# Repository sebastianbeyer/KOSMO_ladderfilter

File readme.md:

A Kosmo version of the [Kassutronics transistor ladder filter](https://kassu2000.blogspot.com/2018/07/transistor-ladder-filter.html).

Find the documentation **and BOM** here: (https://github.com/kassu/kassutronics/tree/master/documentation/Transistor%20Ladder%20Filter)

You need to match the transistors, which is a bit boring. Those that I got where
already pretty close (within the recommended 2mV limit), but some outliers, so
maaaybe you could just try without matching.

# How to make the PCBs

Go download the latest gerber files [here](https://github.com/sebastianbeyer/KOSMO_ladderfilter/releases/latest).
Then send them to your favorite PCB Manufacturer (I use jlcpcb). Make sure you
check "Specify a location" at "Remove Order Number" for the panel.

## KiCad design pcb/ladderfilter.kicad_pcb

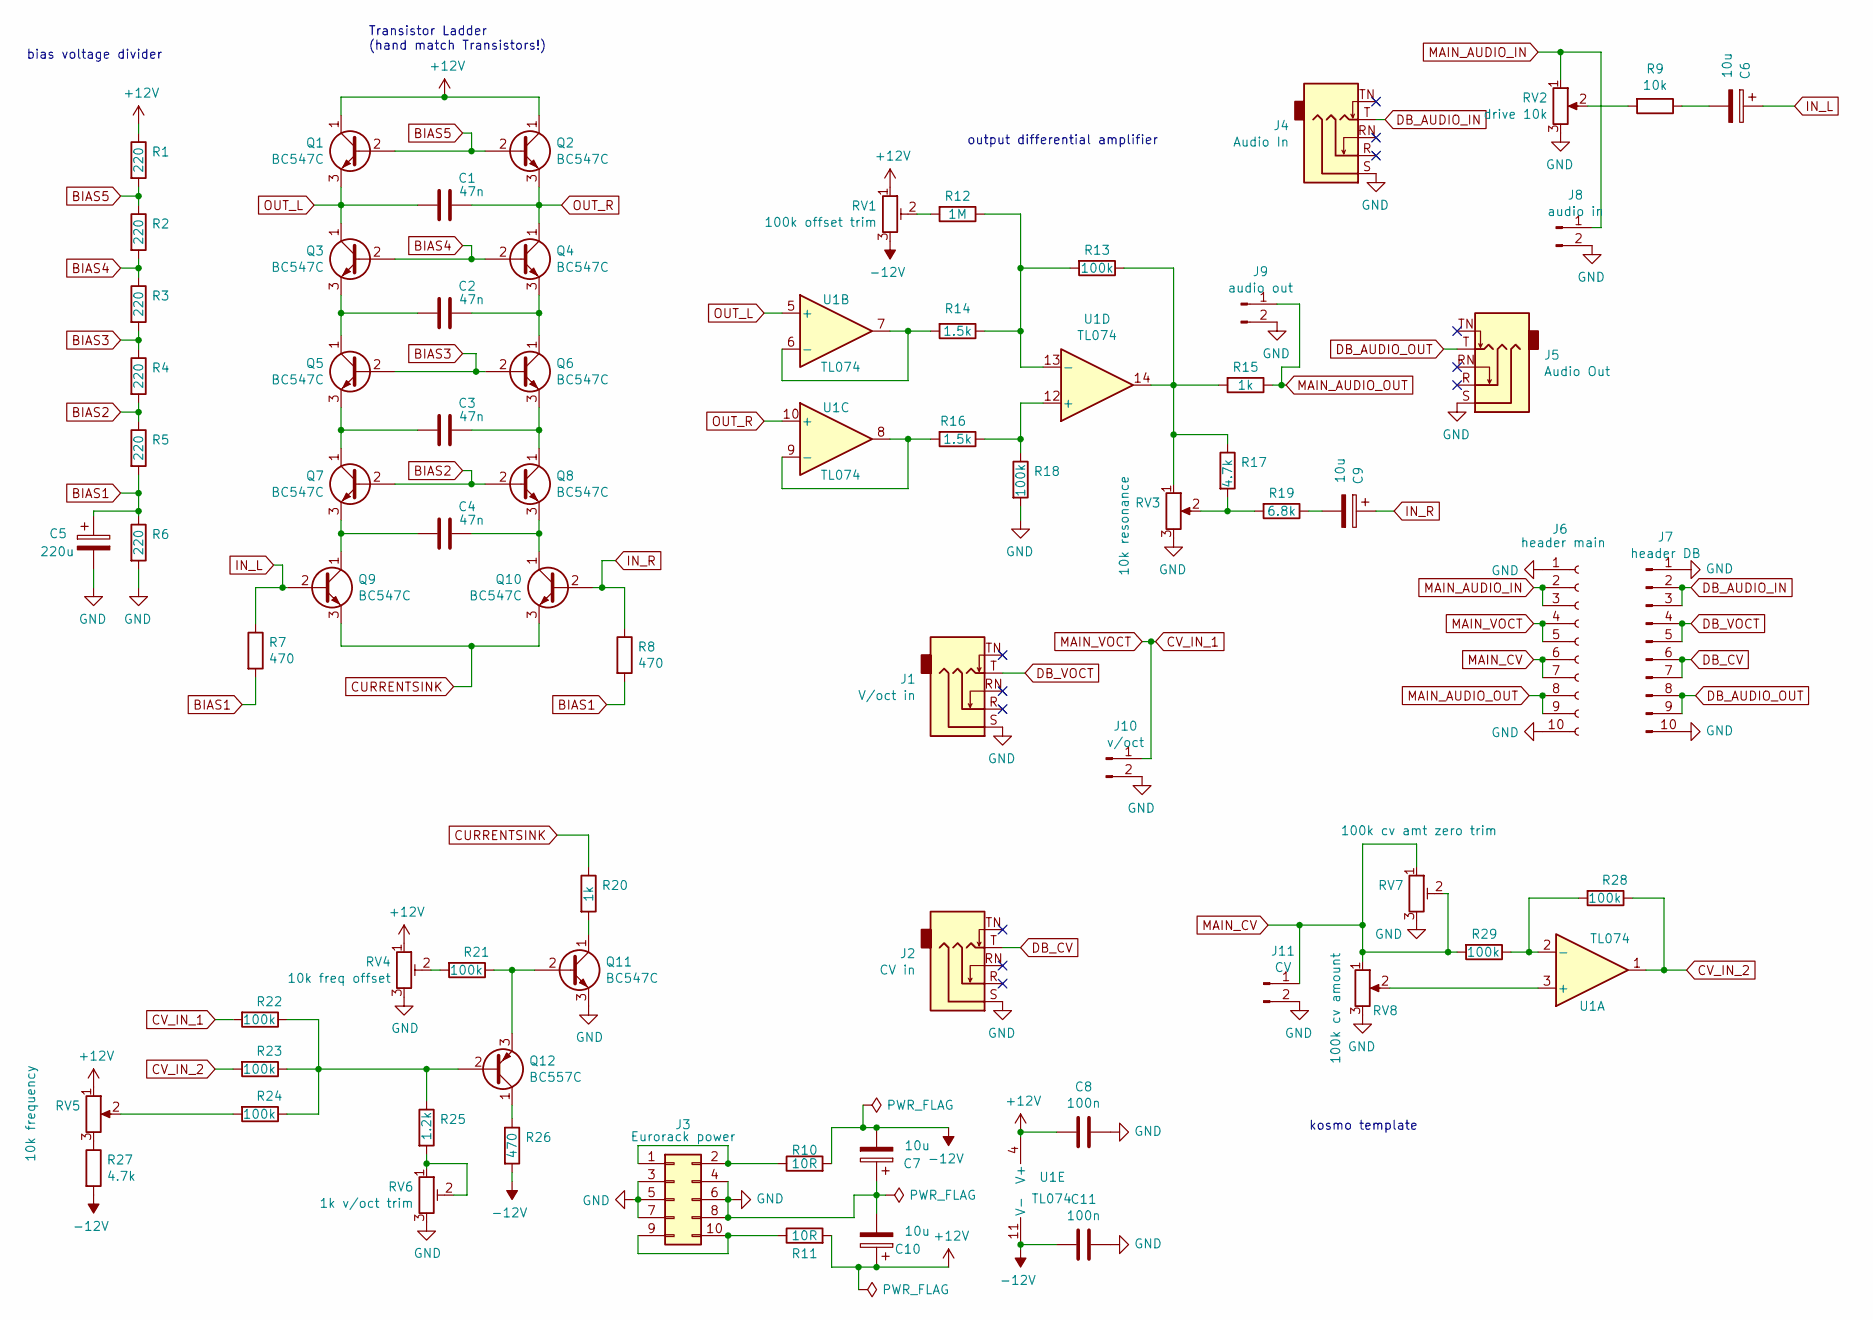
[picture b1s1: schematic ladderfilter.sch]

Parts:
C1, C2, C3, C4: 47n; C_Rect_L7.2mm_W2.5mm_P5.00mm_FKS2_FKP2_MKS2_MKP2
C5: 220u; CP_Radial_D5.0mm_P2.00mm
C6, C7, C9, C10: 10u; CP_Radial_D5.0mm_P2.00mm
C8, C11: 100n; C_Disc_D4.7mm_W2.5mm_P5.00mm
J1: V/oct in; Jack_6.35mm_PJ_629HAN
J2: CV in; Jack_6.35mm_PJ_629HAN
J3: Eurorack power; Multicomp_MC9A12-1034_2x05_P2.54mm_Vertical
J4: Audio In; Jack_6.35mm_PJ_629HAN
J5: Audio Out; Jack_6.35mm_PJ_629HAN
J6: header main; PinSocket_1x10_P2.54mm_Vertical
J7: header DB; PinHeader_1x10_P2.54mm_Vertical
J8: audio in; Molex_KK-254_AE-6410-02A_1x02_P2.54mm_Vertical
J9: audio out; Molex_KK-254_AE-6410-02A_1x02_P2.54mm_Vertical
J10: v/oct; Molex_KK-254_AE-6410-02A_1x02_P2.54mm_Vertical
J11: CV; Molex_KK-254_AE-6410-02A_1x02_P2.54mm_Vertical
Q1, Q2, Q3, Q4, Q5, Q6, Q7, Q8, Q9, Q10, Q11: BC547C; TO-92_Inline_Wide
Q12: BC557C; TO-92_Inline_Wide
R1, R2, R3, R4, R5, R6: 220; R_Axial_DIN0207_L6.3mm_D2.5mm_P7.62mm_Horizontal_silkvalue
R7, R8, R26: 470; R_Axial_DIN0207_L6.3mm_D2.5mm_P7.62mm_Horizontal_silkvalue
R9: 10k; R_Axial_DIN0207_L6.3mm_D2.5mm_P7.62mm_Horizontal_silkvalue
R10, R11: 10R; R_Axial_DIN0207_L6.3mm_D2.5mm_P7.62mm_Horizontal_silkvalue
R12: 1M; R_Axial_DIN0207_L6.3mm_D2.5mm_P7.62mm_Horizontal_silkvalue
R13, R18, R21, R22, R23, R24, R28, R29: 100k; R_Axial_DIN0207_L6.3mm_D2.5mm_P7.62mm_Horizontal_silkvalue
R14, R16: 1.5k; R_Axial_DIN0207_L6.3mm_D2.5mm_P7.62mm_Horizontal_silkvalue
R15, R20: 1k; R_Axial_DIN0207_L6.3mm_D2.5mm_P7.62mm_Horizontal_silkvalue
R17, R27: 4.7k; R_Axial_DIN0207_L6.3mm_D2.5mm_P7.62mm_Horizontal_silkvalue
R19: 6.8k; R_Axial_DIN0207_L6.3mm_D2.5mm_P7.62mm_Horizontal_silkvalue
R25: 1.2k; R_Axial_DIN0207_L6.3mm_D2.5mm_P7.62mm_Horizontal_silkvalue
RV1: 100k offset trim; Potentiometer_Bourns_3296W_Vertical
RV2: drive 10k; Potentiometer_Alps_RK09K_Single_Vertical
RV3: 10k resonance; Potentiometer_Alps_RK09K_Single_Vertical
RV4: 10k freq offset; Potentiometer_Bourns_3296W_Vertical
RV5: 10k frequency; Potentiometer_Alps_RK09K_Single_Vertical
RV6: 1k v/oct trim; Potentiometer_Bourns_3296W_Vertical
RV7: 100k cv amt zero trim; Potentiometer_Bourns_3296W_Vertical
RV8: 100k cv amount; Potentiometer_Alps_RK09K_Single_Vertical
U1: TL074; DIP-14_W7.62mm_Socket_LongPads

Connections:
+12V: C8.2, C10.1, Q1.1 (C), Q2.1 (C), R1.1, R11.2, RV1.1, RV4.1, RV5.1, U1.4 (V+)
-12V: C7.2, C11.2, R10.2, R26.2, R27.2, RV1.3, U1.11 (V-)
BIAS1: C5.1, R5.2, R6.1, R7.2, R8.2
BIAS2: Q7.2 (B), Q8.2 (B), R4.2, R5.1
BIAS3: Q5.2 (B), Q6.2 (B), R3.2, R4.1
BIAS4: Q3.2 (B), Q4.2 (B), R2.2, R3.1
BIAS5: Q1.2 (B), Q2.2 (B), R1.2, R2.1
CURRENTSINK: Q9.3 (E), Q10.3 (E), R20.1
CV_IN_1: J6.4, J6.5, J10.1, R22.2
CV_IN_2: R23.2, R28.1, U1.1
GND: C5.2, C7.1, C8.1, C10.2, C11.1, J1.S, J2.S, J3.3, J3.4, J3.5, J3.6, J3.7, J3.8, J4.S, J5.S, J6.1, J6.10, J7.1, J7.10, J8.2, J9.2, J10.2, J11.2, Q11.3 (E), R6.2, R18.2, RV2.3, RV3.3, RV4.3, RV6.3, RV7.3, RV8.3
IN_L: C6.1, Q9.2 (B), R7.1
IN_R: C9.1, Q10.2 (B), R8.1
MAIN_AUDIO_IN: J6.2, J6.3, J8.1, RV2.1
MAIN_AUDIO_OUT: J6.8, J6.9, J9.1, R15.1
MAIN_CV: J6.6, J6.7, J11.1, R29.2, RV7.1, RV7.2, RV8.1
unnamed: C2.1, Q4.3 (E), Q6.1 (C)
unnamed: C2.2, Q3.3 (E), Q5.1 (C)
unnamed: C3.1, Q6.3 (E), Q8.1 (C)
unnamed: C3.2, Q5.3 (E), Q7.1 (C)
unnamed: C4.1, Q8.3 (E), Q10.1 (C)
unnamed: C4.2, Q7.3 (E), Q9.1 (C)
unnamed: C6.2, R9.1
unnamed: C9.2, R19.1
unnamed: J1.T, J7.4, J7.5
unnamed: J2.T, J7.6, J7.7
unnamed: J3.1, J3.2, R10.1
unnamed: J3.9, J3.10, R11.1
unnamed: J4.T, J7.2, J7.3
unnamed: J5.T, J7.8, J7.9
unnamed: Q11.1 (C), R20.2
unnamed: Q11.2 (B), Q12.3 (E), R21.1
unnamed: Q12.1 (C), R26.1
unnamed: Q12.2 (B), R22.1, R23.1, R24.1, R25.1
unnamed: R9.2, RV2.2
unnamed: R12.1, R13.2, R14.1, U1.13 (-)
unnamed: R12.2, RV1.2
unnamed: R13.1, R15.2, R17.1, RV3.1, U1.14
unnamed: R14.2, U1.6 (-), U1.7
unnamed: R16.1, R18.1, U1.12 (+)
unnamed: R16.2, U1.8, U1.9 (-)
unnamed: R17.2, R19.2, RV3.2
unnamed: R21.2, RV4.2
unnamed: R24.2, RV5.2
unnamed: R25.2, RV6.1, RV6.2
unnamed: R27.1, RV5.3
unnamed: R28.2, R29.1, U1.2 (-)
unnamed: RV8.2, U1.3 (+)
OUT_L: C1.2, Q1.3 (E), Q3.1 (C), U1.5 (+)
OUT_R: C1.1, Q2.3 (E), Q4.1 (C), U1.10 (+)

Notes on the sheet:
kosmo template
bias voltage divider
Transistor Ladder (hand match Transistors!)
output differential amplifier

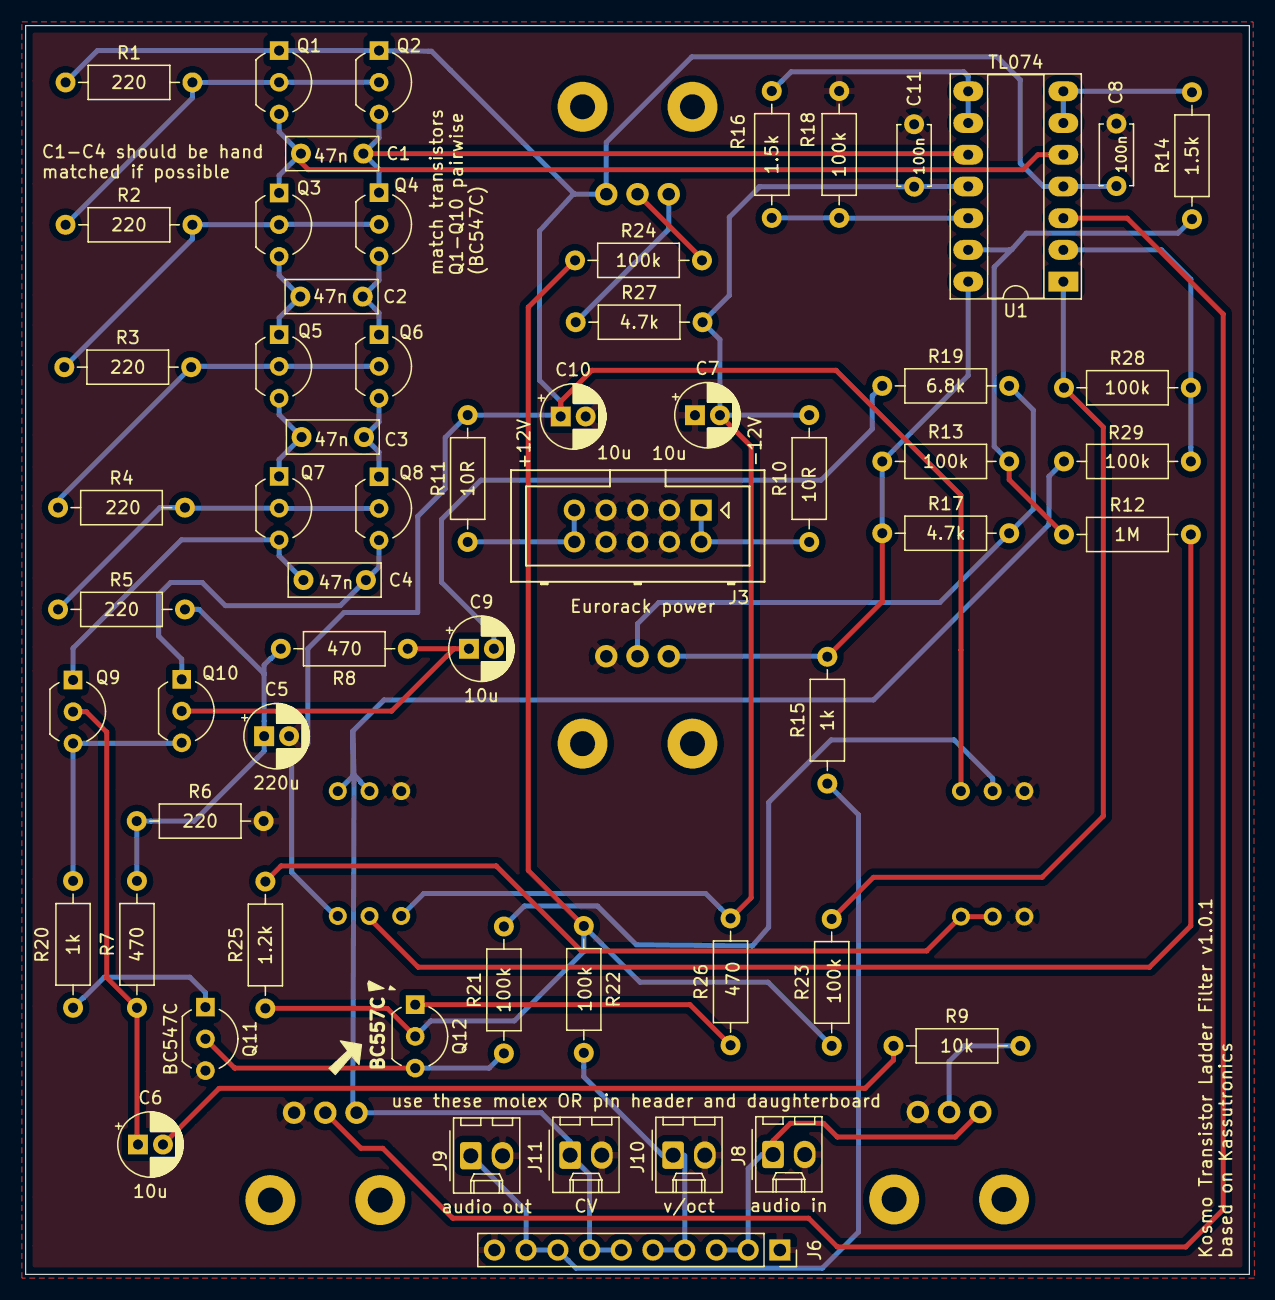
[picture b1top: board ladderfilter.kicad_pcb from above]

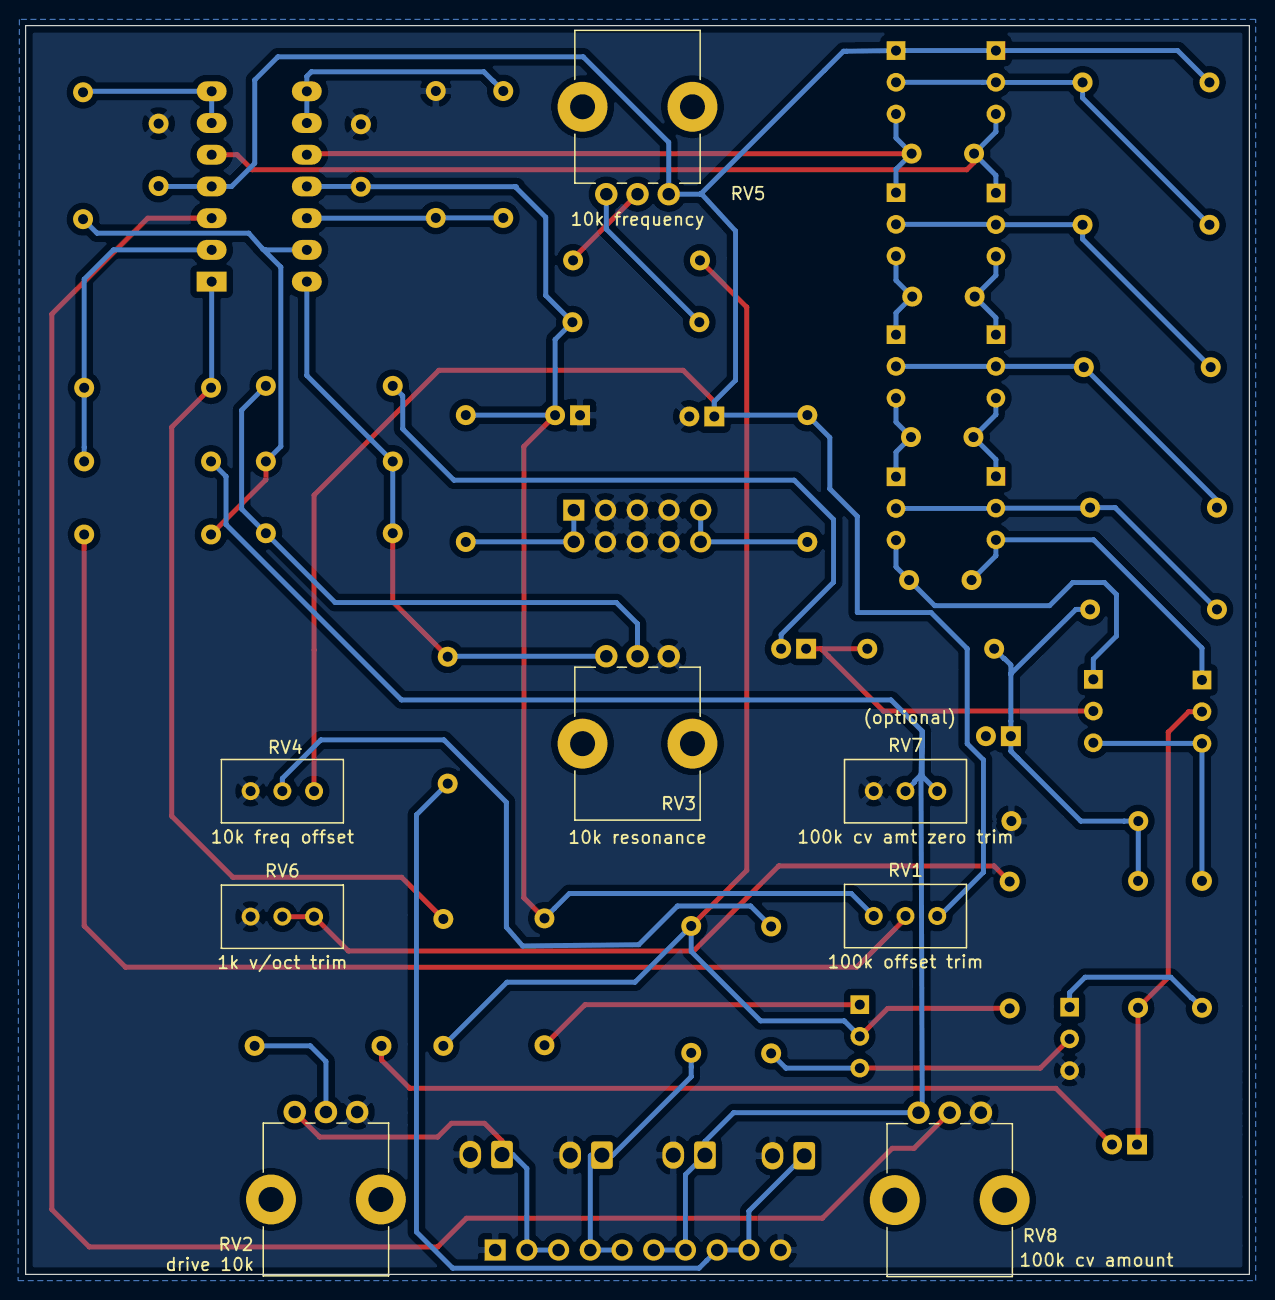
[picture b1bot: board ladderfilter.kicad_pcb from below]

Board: 2 copper layers, 98.0 x 100.0 mm, 67 parts (8 on the bottom side), 46 nets.

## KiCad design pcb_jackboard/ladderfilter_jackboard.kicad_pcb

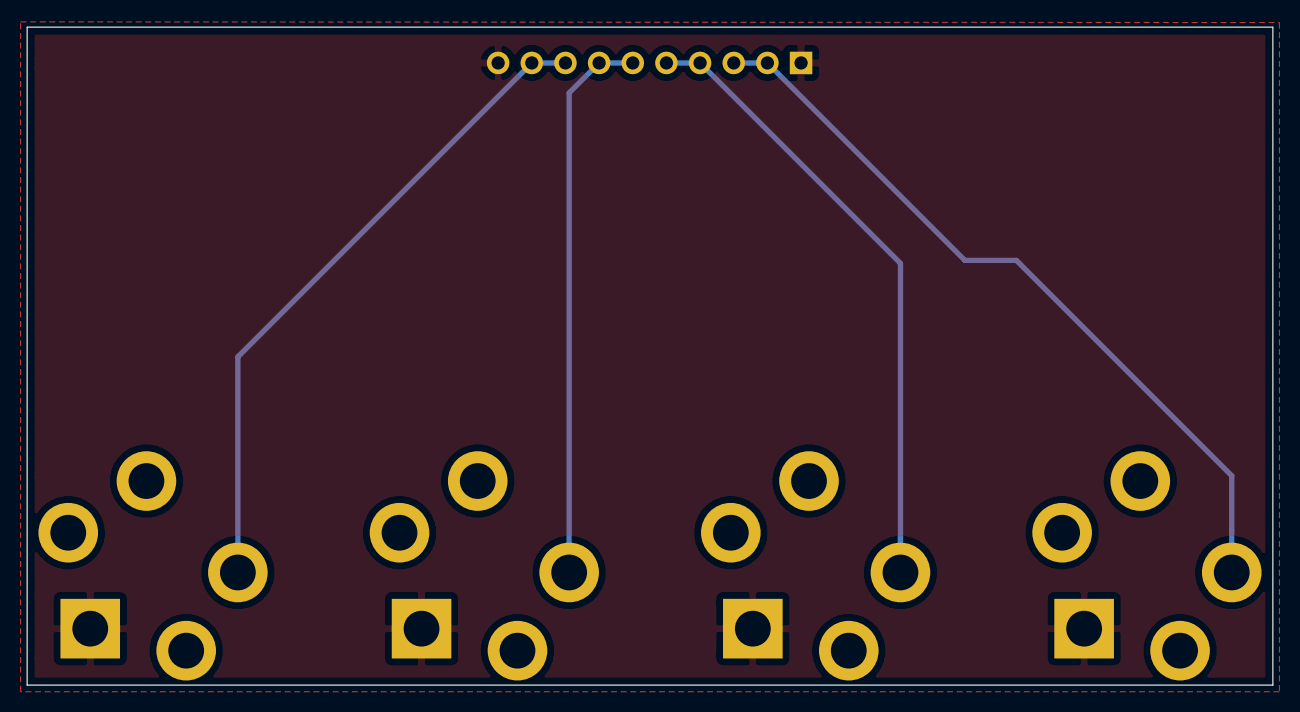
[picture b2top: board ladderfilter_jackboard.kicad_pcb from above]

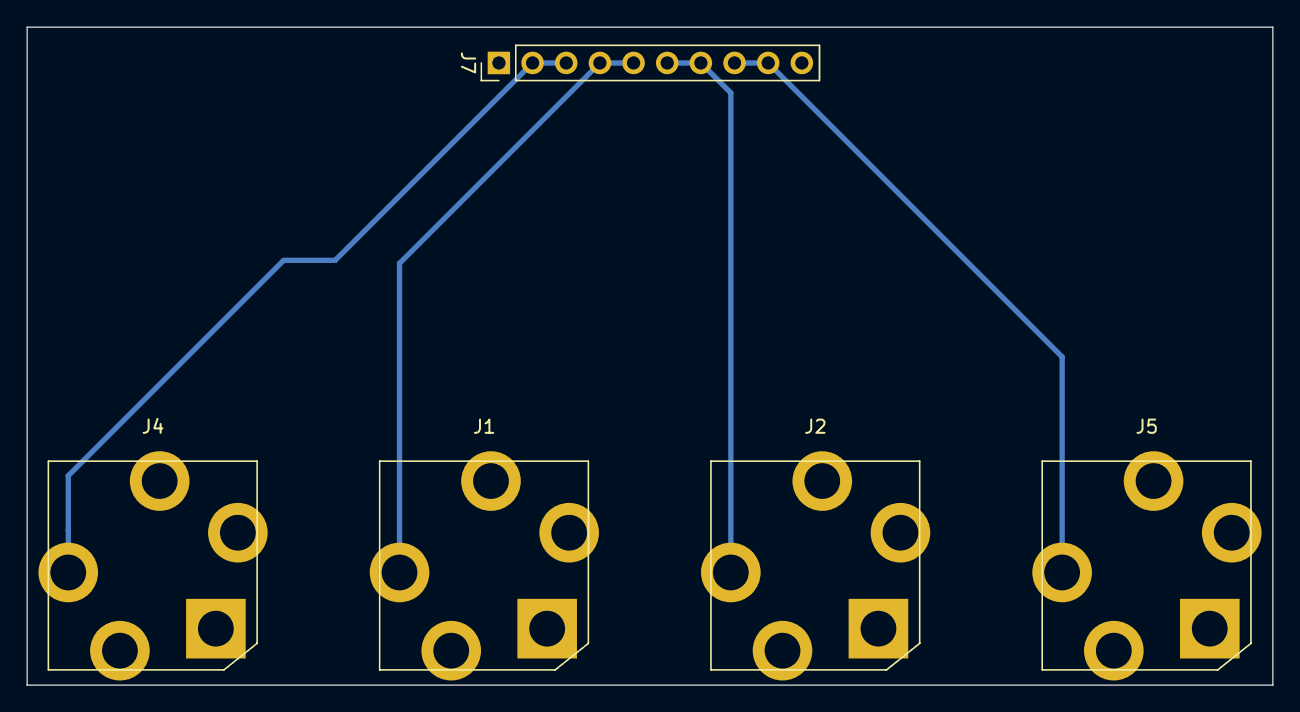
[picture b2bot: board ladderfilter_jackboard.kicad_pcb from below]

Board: 2 copper layers, 94.0 x 49.7 mm, 5 parts (5 on the bottom side), 5 nets.

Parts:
J1: V/oct in; Jack_6.35mm_PJ_629HAN
J2: CV in; Jack_6.35mm_PJ_629HAN
J4: Audio In; Jack_6.35mm_PJ_629HAN
J5: Audio Out; Jack_6.35mm_PJ_629HAN
J7: header DB; PinHeader_1x10_P2.54mm_Vertical

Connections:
DB_AUDIO_IN: J4.T, J7.2, J7.3
DB_AUDIO_OUT: J5.T, J7.8, J7.9
DB_CV: J2.T, J7.6, J7.7
DB_VOCT: J1.T, J7.4, J7.5
GND: J1.S, J2.S, J4.S, J5.S, J7.1, J7.10

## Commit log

2020-07-10 initial
2020-07-10 add readme
2020-07-10 add releases link to readme
2020-07-10 make the image smaller
2020-07-10 make the image smaller2
2020-07-10 make the image smaller3
